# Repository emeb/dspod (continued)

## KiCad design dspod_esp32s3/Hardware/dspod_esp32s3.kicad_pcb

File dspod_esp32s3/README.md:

# dspod_esp32s3

The dspod_esp32s3 is a daughterboard comprising an ESP32 S3 MCU with 4MB Flash, 2MB PSRAM, USB and GPIO + audio I/O.

## Abstract

This board is a small 32-pin device with the following features:

* ESP32S3H4R2 MCU
  - 56-pin QFN package
  - Dual-core Extensa LX7 CPUs 
  - 512kB SRAM
  - USB, I2C, SPI, ADC, GPIO, WiFi, etc on-chip
  - 4MB flash in package
  - 2MB PSRAM in package
* USB-C connector, full-speed host/device
* Nuvoton NAU88C22 stereo codec
* Misc GPIO
  - SPI
  - I2C
  - GPIO
* Four channels of 3.3V multiplexed A/D input
* RF connector for off-board antenna

## Design Materials

* [Schematic](./doc/dspod_esp32s3_sch.pdf)

## Hardware

The hardware design is provided in Kicad 9.x format in the [Hardware](./Hardware) directory.

## Firmware

Firmware is available in the [Firmware](./Firmware) directory.

## Results

The hardware implementation is very similar to an earlier project I did [S3GTA](https://github.com/emeb/S3GTA) so there weren't any big surprises in the overall performance. The CV conversions with the on-chip ADC work fine with a bit of filtering and the encoder/button/LCD-based UI is virtually identical to that on the other three dspod projects so it feels pretty much the same regardless of which instance is in use. The basic effects - filters, delays, reverbs, pitch, frequency and phase shifts - all work the same way and use roughly the right amount of CPU based on their complexity. There are a few unique things about this hardware with respect to the other dspod daughterboards though:

#### PSRAM

The ESP32S3 has a QSPI interface for flash and PSRAM that maps these serial devices into the CPU address space like as though it were internal memory (with slow access times). The H4R2 variant has 2MB PSRAM built in and it works well for audio delay buffering without incurring too much processing overhead.

#### Dual Cores

There are two instances of the Tensilica Extensa LX7 CPU core built in and the vendor's FreeRTOS-based development tools make it very easy to use both. The current effects application code does make use of this, running the UI and ADC code on the first core and the audio DSP on the second core - this hasn't made much difference in overall performance as the current audio code is not particularly taxing, but may help in future experiments that push the boundaries.

#### DSP

The LX7 CPUs have hardware floating point and some vector instructions for accelerating math / DSP operations, and the ESP-IDF has a library of optimized assembly routines for common DSP such as transforms, correlations, windowing, etc. and I've done some experiments with their example code to evaluate the performance. Their radix 4 complex FFT is very efficient, doing better on a per-cycle basis than the ARM CMSIS radix 8 FFT that I use in H7R3 spectral effects. Despite this, the slower processor speed (240MHz max) of the ESP32S3 vs the 600MHz STM32H7R3 means that it cannot complete the required operations within the time allowed so it's not a good match for these algorithms. 

#### RF

Naturally, the ESP32 family has WiFi and Bluetooth capability and I've provided hardware on this board to enable experiments with this. There is a 50-ohm matching network onboard and a uFL connector for use with readily available antennas. Early testing with some of the ESP-IDF WiFi examples indicates that RF performance is sufficient to connect to a nearby AP and the usual APs seen in my area by other devices are visible to the dspod with an inexpensive antenna. 

## Going Further

While I've explored most of the highlights, there are a few aspects of this MCU I'd like to explore further:

#### RF

While WiFi performance appears usable, I'd like to experiment with audio streaming via WiFi and using the dspod as a Bluetooth audio device.

#### Algorithms

The current complement of effects algorithms are fairly lightweight so I'm looking forward to trying out some more complex things, and while spectral processing is probably not practical, there is CPU bandwidth and RAM capacity for more complex time domain effects.

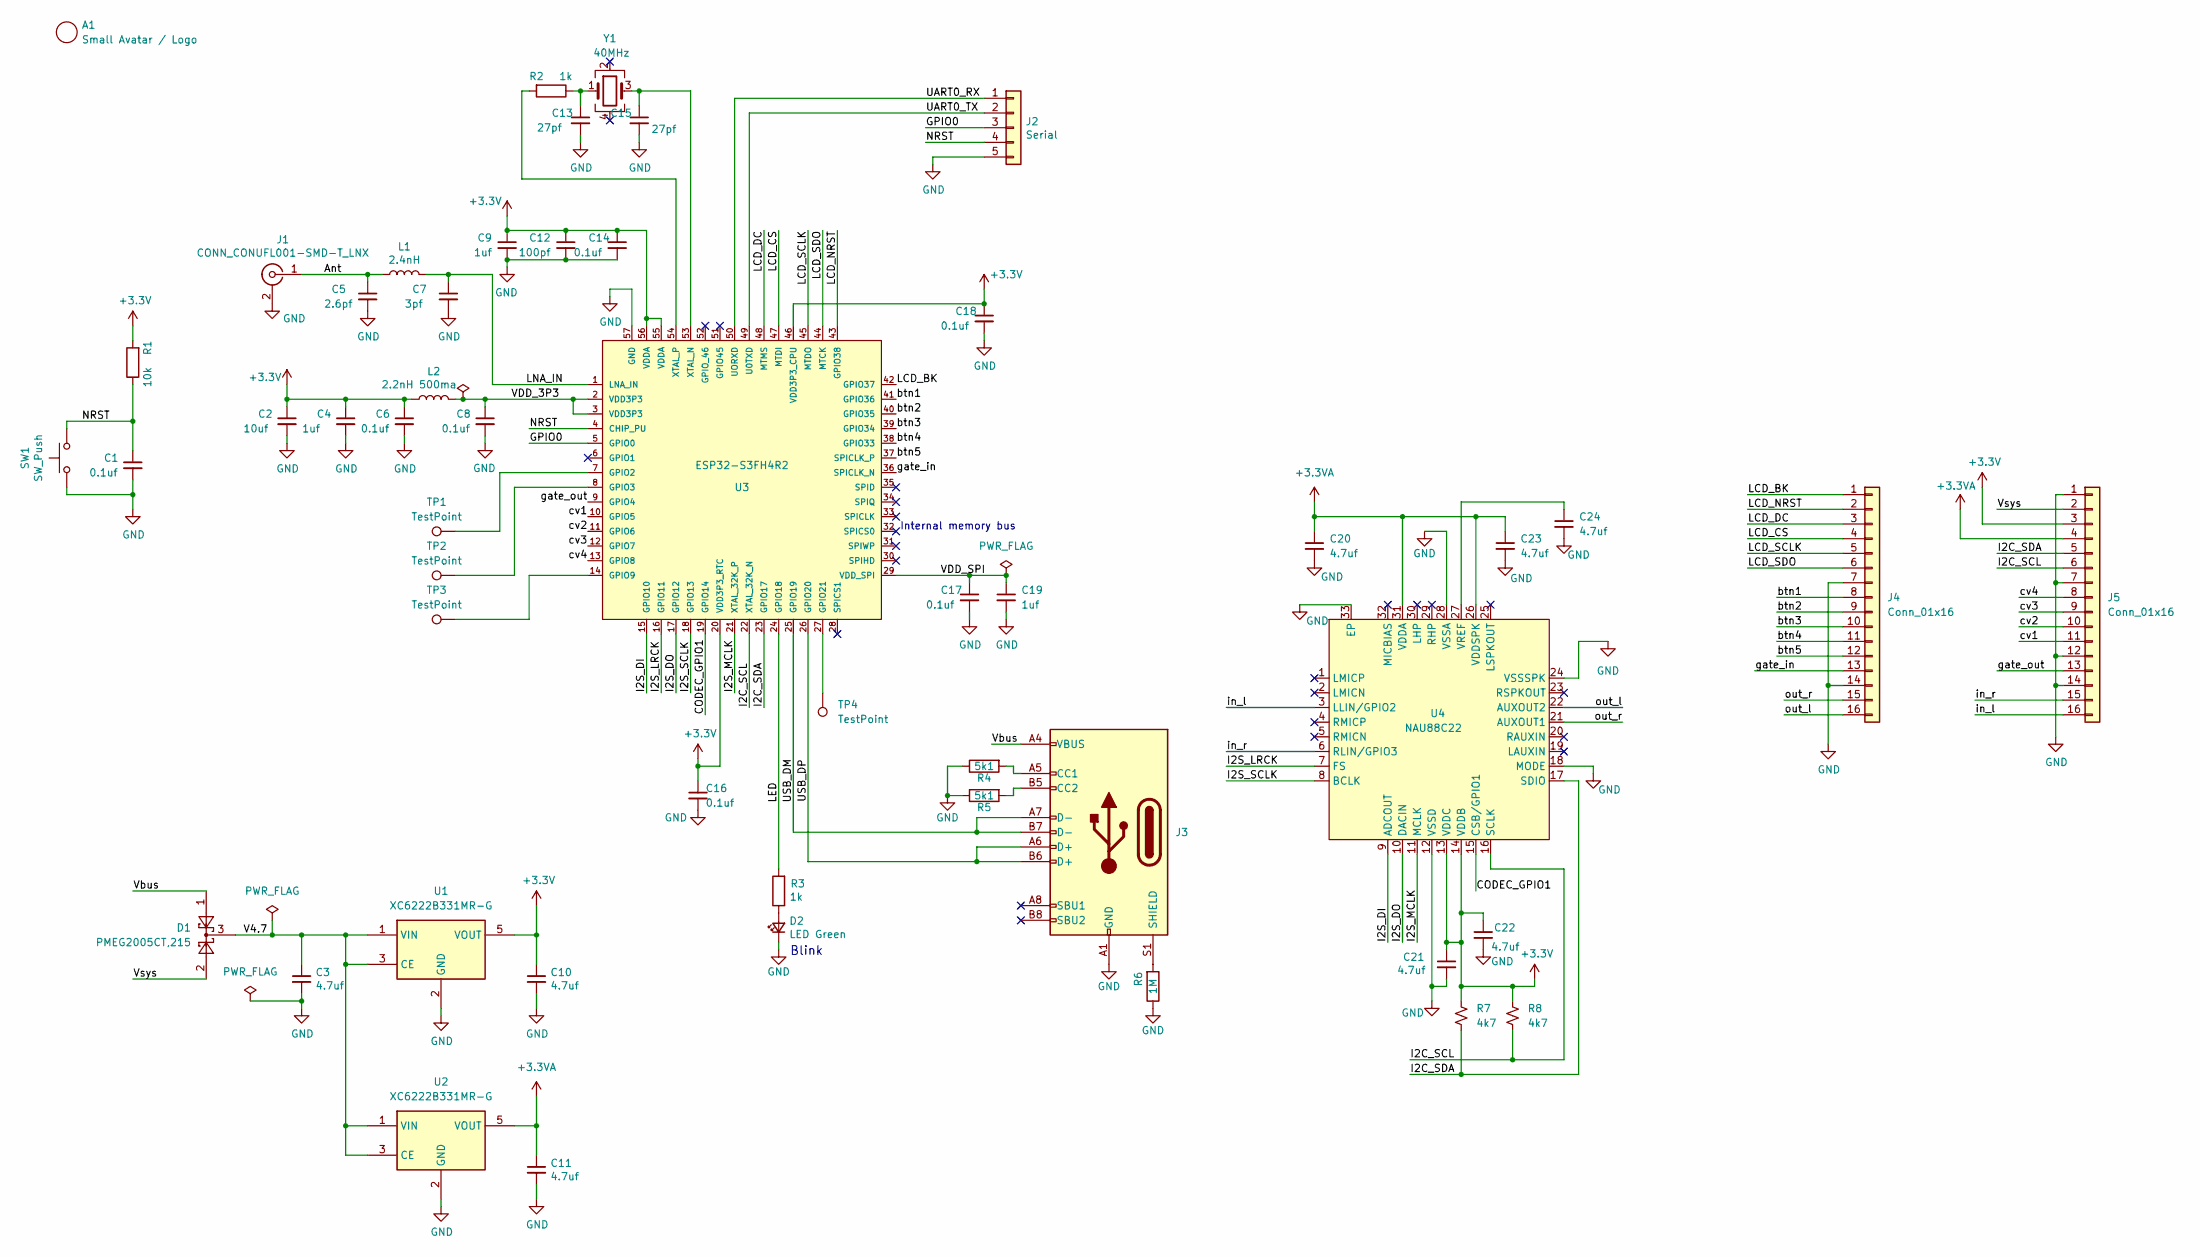
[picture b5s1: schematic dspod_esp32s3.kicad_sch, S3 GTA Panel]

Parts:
A1: Small Avatar / Logo; avatar_small
C1, C6, C8, C14, C16, C17, C18: 0.1uf; C_0402_1005Metric
C2: 10uf; C_0805_2012Metric
C3, C10, C11, C20, C21, C22, C23, C24: 4.7uf; C_0402_1005Metric
C4, C9, C19: 1uf; C_0402_1005Metric
C5: 2.6pf; C_0402_1005Metric
C7: 3pf; C_0402_1005Metric
C12: 100pf; C_0402_1005Metric
C13, C15: 27pf; C_0402_1005Metric
D1: PMEG2005CT,215; SOT-23
D2: LED Green; LED_0603_1608Metric
J1: CONN_CONUFL001-SMD-T_LNX; CONUFL001-SMD-T
J2: Serial; PinHeader_1x05_P2.54mm_Horizontal
J3: USB_C_Receptacle_USB2.0; USB_C_Receptacle_HRO_TYPE-C-31-M-12
J4, J5: Conn_01x16; PinHeader_1x16_P2.54mm_Vertical
L1: 2.4nH; C_0603_1608Metric
L2: 2.2nH 500ma; C_0603_1608Metric
R1: 10k; R_0402_1005Metric
R2, R3: 1k; R_0402_1005Metric
R4, R5: 5k1; R_0402_1005Metric
R6: 1M; R_0402_1005Metric
R7, R8: 4k7; R_0402_1005Metric
SW1: SW_Push; SW_Push_1P1T_NO_CK_KMR2
TP1, TP2, TP3, TP4: TestPoint; TestPoint_Pad_D1.0mm
U1, U2: XC6222B331MR-G; SOT-23-5
U3: ESP32-S3FH4R2; ESP32-S3; mouser part number 356-ESP32-S2; digikey description RX TXRX MOD WIFI SURFACE MOUNT
U4: NAU88C22; QFN-32-1EP_5x5mm_P0.5mm_EP3.1x3.1mm
Y1: 40MHz; Crystal_SMD_3225-4Pin_3.2x2.5mm

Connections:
+3.3V: C2.1, C4.1, C6.1, C9.1, C10.1, C12.1, C14.1, C16.1, C18.1, C21.1, C22.1, J5.3, L2.1, R1.2, R7.2, R8.2, U1.5 (VOUT), U3.20 (VDD3P3_RTC), U3.46 (VDD3P3_CPU), U3.55 (VDDA), U3.56 (VDDA), U4.13 (VDDC), U4.14 (VDDB)
+3.3VA: C11.1, C20.1, C23.1, J5.4, U2.5 (VOUT), U4.26 (VDDSPK), U4.31 (VDDA)
/Ant: C5.1, J1.1 (SIG), L1.1
/CODEC_GPIO1: U3.19 (GPIO14), U4.15 (CSB/GPIO1)
/GPIO0: J2.3, U3.5 (GPIO0)
/I2C_SCL: J5.6, R8.1, U3.22 (XTAL_32K_N), U4.16 (SCLK)
/I2C_SDA: J5.5, R7.1, U3.23 (GPIO17), U4.17 (SDIO)
/I2S_DI: U3.15 (GPIO10), U4.9 (ADCOUT)
/I2S_DO: U3.17 (GPIO12), U4.10 (DACIN)
/I2S_LRCK: U3.16 (GPIO11), U4.7 (FS)
/I2S_MCLK: U3.21 (XTAL_32K_P), U4.11 (MCLK)
/I2S_SCLK: U3.18 (GPIO13), U4.8 (BCLK)
/LCD_BK: J4.1, U3.42 (GPIO37)
/LCD_CS: J4.4, U3.47 (MTDI)
/LCD_DC: J4.3, U3.48 (MTMS)
/LCD_NRST: J4.2, U3.43 (GPIO38)
/LCD_SCLK: J4.5, U3.45 (MTDO)
/LCD_SDO: J4.6, U3.44 (MTCK)
/LED: R3.2, U3.24 (GPIO18)
/LNA_IN: C7.1, L1.2, U3.1 (LNA_IN)
/NRST: C1.1, J2.4, R1.1, SW1.1, U3.4 (CHIP_PU)
/UART0_RX: J2.1, U3.50 (UORXD)
/UART0_TX: J2.2, U3.49 (U0TXD)
/USB_DM: J3.A7 (D-), J3.B7 (D-), U3.25 (GPIO19)
/USB_DP: J3.A6 (D+), J3.B6 (D+), U3.26 (GPIO20)
/V4.7: C3.1, D1.3, U1.1 (VIN), U1.3 (CE), U2.1 (VIN), U2.3 (CE)
/VDD_3P3: C8.1, L2.2, U3.2 (VDD3P3), U3.3 (VDD3P3)
/VDD_SPI: C17.1, C19.1, U3.29 (VDD_SPI)
/Vbus: D1.1, J3.A4 (VBUS), J3.A9 (VBUS), J3.B4 (VBUS), J3.B9 (VBUS)
/Vsys: D1.2, J5.2
/btn1: J4.8, U3.41 (GPIO36)
/btn2: J4.9, U3.40 (GPIO35)
/btn3: J4.10, U3.39 (GPIO34)
/btn4: J4.11, U3.38 (GPIO33)
/btn5: J4.12, U3.37 (SPICLK_P)
/cv1: J5.11, U3.10 (GPIO5)
/cv2: J5.10, U3.11 (GPIO6)
/cv3: J5.9, U3.12 (GPIO7)
/cv4: J5.8, U3.13 (GPIO8)
/gate_in: J4.13, U3.36 (SPICLK_N)
/gate_out: J5.13, U3.9 (GPIO4)
/in_l: J5.16, U4.3 (LLIN/GPIO2)
/in_r: J5.15, U4.6 (RLIN/GPIO3)
/out_l: J4.16, U4.22 (AUXOUT2)
/out_r: J4.15, U4.21 (AUXOUT1)
GND: C1.2, C2.2, C3.2, C4.2, C5.2, C6.2, C7.2, C8.2, C9.2, C10.2, C11.2, C12.2, C13.2, C14.2, C15.2, C16.2, C17.2, C18.2, C19.2, C20.2, C21.2, C22.2, C23.2, C24.2, D2.1 (K), J1.2 (GND), J2.5, J3.A1 (GND), J3.A12 (GND), J3.B1 (GND), J3.B12 (GND), J4.7, J4.14, J5.1, J5.7, J5.12, J5.14, R4.1, R5.1, R6.1, SW1.2, U1.2 (GND), U2.2 (GND), U3.57 (GND), U4.12 (VSSD), U4.18 (MODE), U4.24 (VSSSPK), U4.28 (VSSA), U4.33 (EP)
unnamed: C13.1, R2.1, Y1.1
unnamed: D2.2 (A), R3.1
unnamed: J3.A5 (CC1), R4.2
unnamed: J3.B5 (CC2), R5.2
unnamed: J3.S1 (SHIELD), R6.2
unnamed: TP1.1, U3.7 (GPIO2)
unnamed: TP2.1, U3.8 (GPIO3)
unnamed: TP3.1, U3.14 (GPIO9)
unnamed: TP4.1, U3.27 (GPIO21)
unnamed: C15.1, U3.53 (XTAL_N), Y1.3
unnamed: R2.2, U3.54 (XTAL_P)
unnamed: C24.1, U4.27 (VREF)

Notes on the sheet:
Internal memory bus
Blink

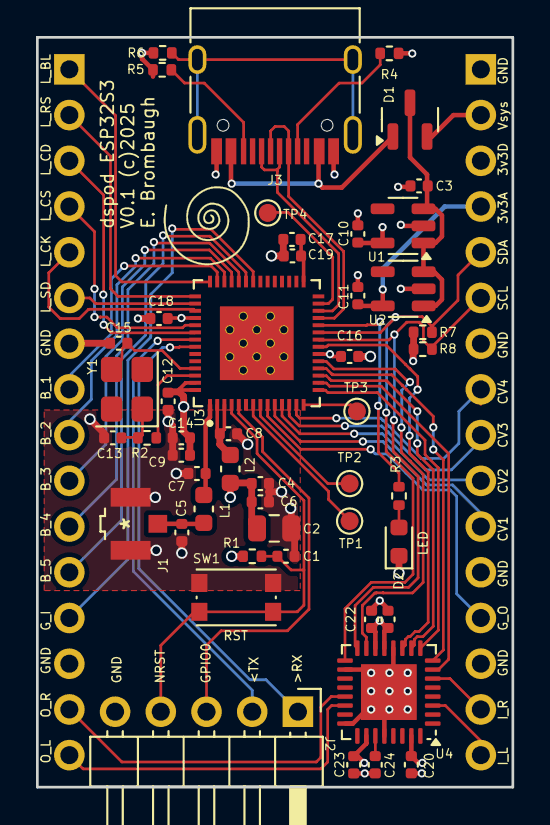
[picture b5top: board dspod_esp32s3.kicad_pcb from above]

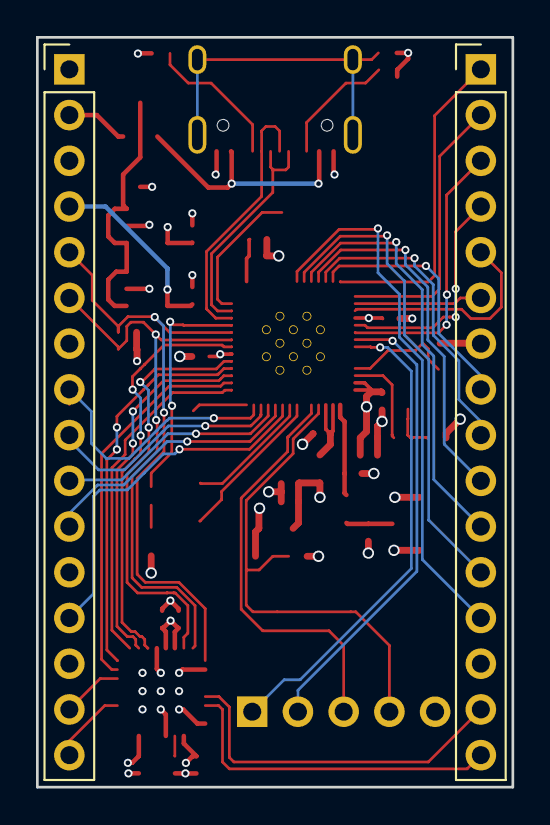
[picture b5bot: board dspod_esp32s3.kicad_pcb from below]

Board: 4 copper layers, 26.4 x 41.7 mm, 52 parts (2 on the bottom side), 58 nets.

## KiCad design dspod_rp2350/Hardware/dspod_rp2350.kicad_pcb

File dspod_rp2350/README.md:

# dspod_rp2350

The dspod_rp2350 is a daughterboard comprising an RP2350A MCU with 4MB Flash, 8MB PSRAM, USB and GPIO + audio I/O.

## Abstract

This board is a small 32-pin device with the following features:

* RP2350 MCU
  - 68-pin QFN package
  - Dual-core Arm Cortex M33 or Hazard3 RISC-V CPUs 
  - 520kB SRAM
  - USB, I2C, SPI, ADC, GPIO, PIO, etc on-chip
* USB-C connector, full-speed host/device
* Nuvoton NAU88C22 stereo codec
* Misc GPIO
  - SPI
  - I2C
  - GPIO
* Four channels of 3.3V multiplexed A/D input

## Design Materials

* [Schematic](./doc/dspod_rp2350_sch.pdf)
* [BOM Spreadsheet](./doc/dspod_rp2350_BOM.ods)

## Hardware

The hardware design is provided in Kicad 9.x format in the [Hardware](./Hardware) directory.

## Firmware

A collection of test programs for exercising all the peripherals of the dspod_rp2350 can be found in the [Firmware](./Firmware) directory.

## Results

Bringing up the hardware drivers and DSP effects application on the RP2350 was remarkably pain-free and performance is reasonable given the manufacturer's published constraints. Following are some observations:

#### I2S Audio

The PIO peripheral works well for implementing I2S formatted serial I/O with DMA into on-chip SRAM buffers. I use a slightly modified version of the original output-only example code that was provided by the manufacturer and was adapted for full-duplex operation by [Jonathan Brodsky](https://github.com/jonbro). 

#### Multicore processing

This is well-supported by the Pico SDK and straightforward to implement. In the DSP effects application the code was split between the foreground UI and ADC polling running on core 0 and the DSP running on core 1 which worked nicely.

#### PSRAM

The original RP2040 relies on external QSPI flash for nonvolatile storage of code and data and allows execute in-place (XIP) access which maps the external QSPI flash into the CPU address space. This works very well and for the RP2350 a second chip select line and write capability was added that supports RAM. This board uses that capability for audio data buffering and it functions well.

#### Loadable code

An experiment in the effects application was the use of loadable code sections via "overlays". This requires some fancy tricks in the linker and function attributes to pull chunks of executable code from off-chip flash into on-chip CCMRAM on demand in order to improve code execution speed while limiting the resources required for large code bases. This worked well and allows maximum code execution speed while not impacting RAM usage heavily.

#### Clock Speed

As of February 2026, the RP2350 is specified to run at a maximum clock speed of 150MHz with a VREG voltage of 1.1V. Experiments in the user community have shown however that it can be reliably run at much higher speeds if the VREG setting is increased and proper cooling is provided - see this article for details: [Overclocking Raspberry Pi Pico 2](https://learn.pimoroni.com/article/overclocking-the-pico-2). By default, the dspod_rp2350 is set to operate at 159.750MHz - slightly overclocked to provide a nearly perfect 48001Hz audio sample rate, but by changing a few settings in the CMakelists.txt file it's possible to double the clock rate to nearly 320MHz with only a slight increase in the VREG setting (firmware controlled) which significantly improves the CPU loading of the more complex DSP. Further increases may be possible, and if rates near 500MHz are acheivable then FFT-based spectral effects may be feasible on this platform. Further experiments are in process to see where the limits are. 

#### Performance

Overall, the RP2350 platform provides a lot of powerful options for audio DSP, especially if pushed beyond the conservative limits specified by the manufacturer. The MCU itself is one of the least expensive ones tested on the dspod ecosystem despite providing two CPU cores and lots of on-chip SRAM and it has a lot of potential that hasn't been fully explored.

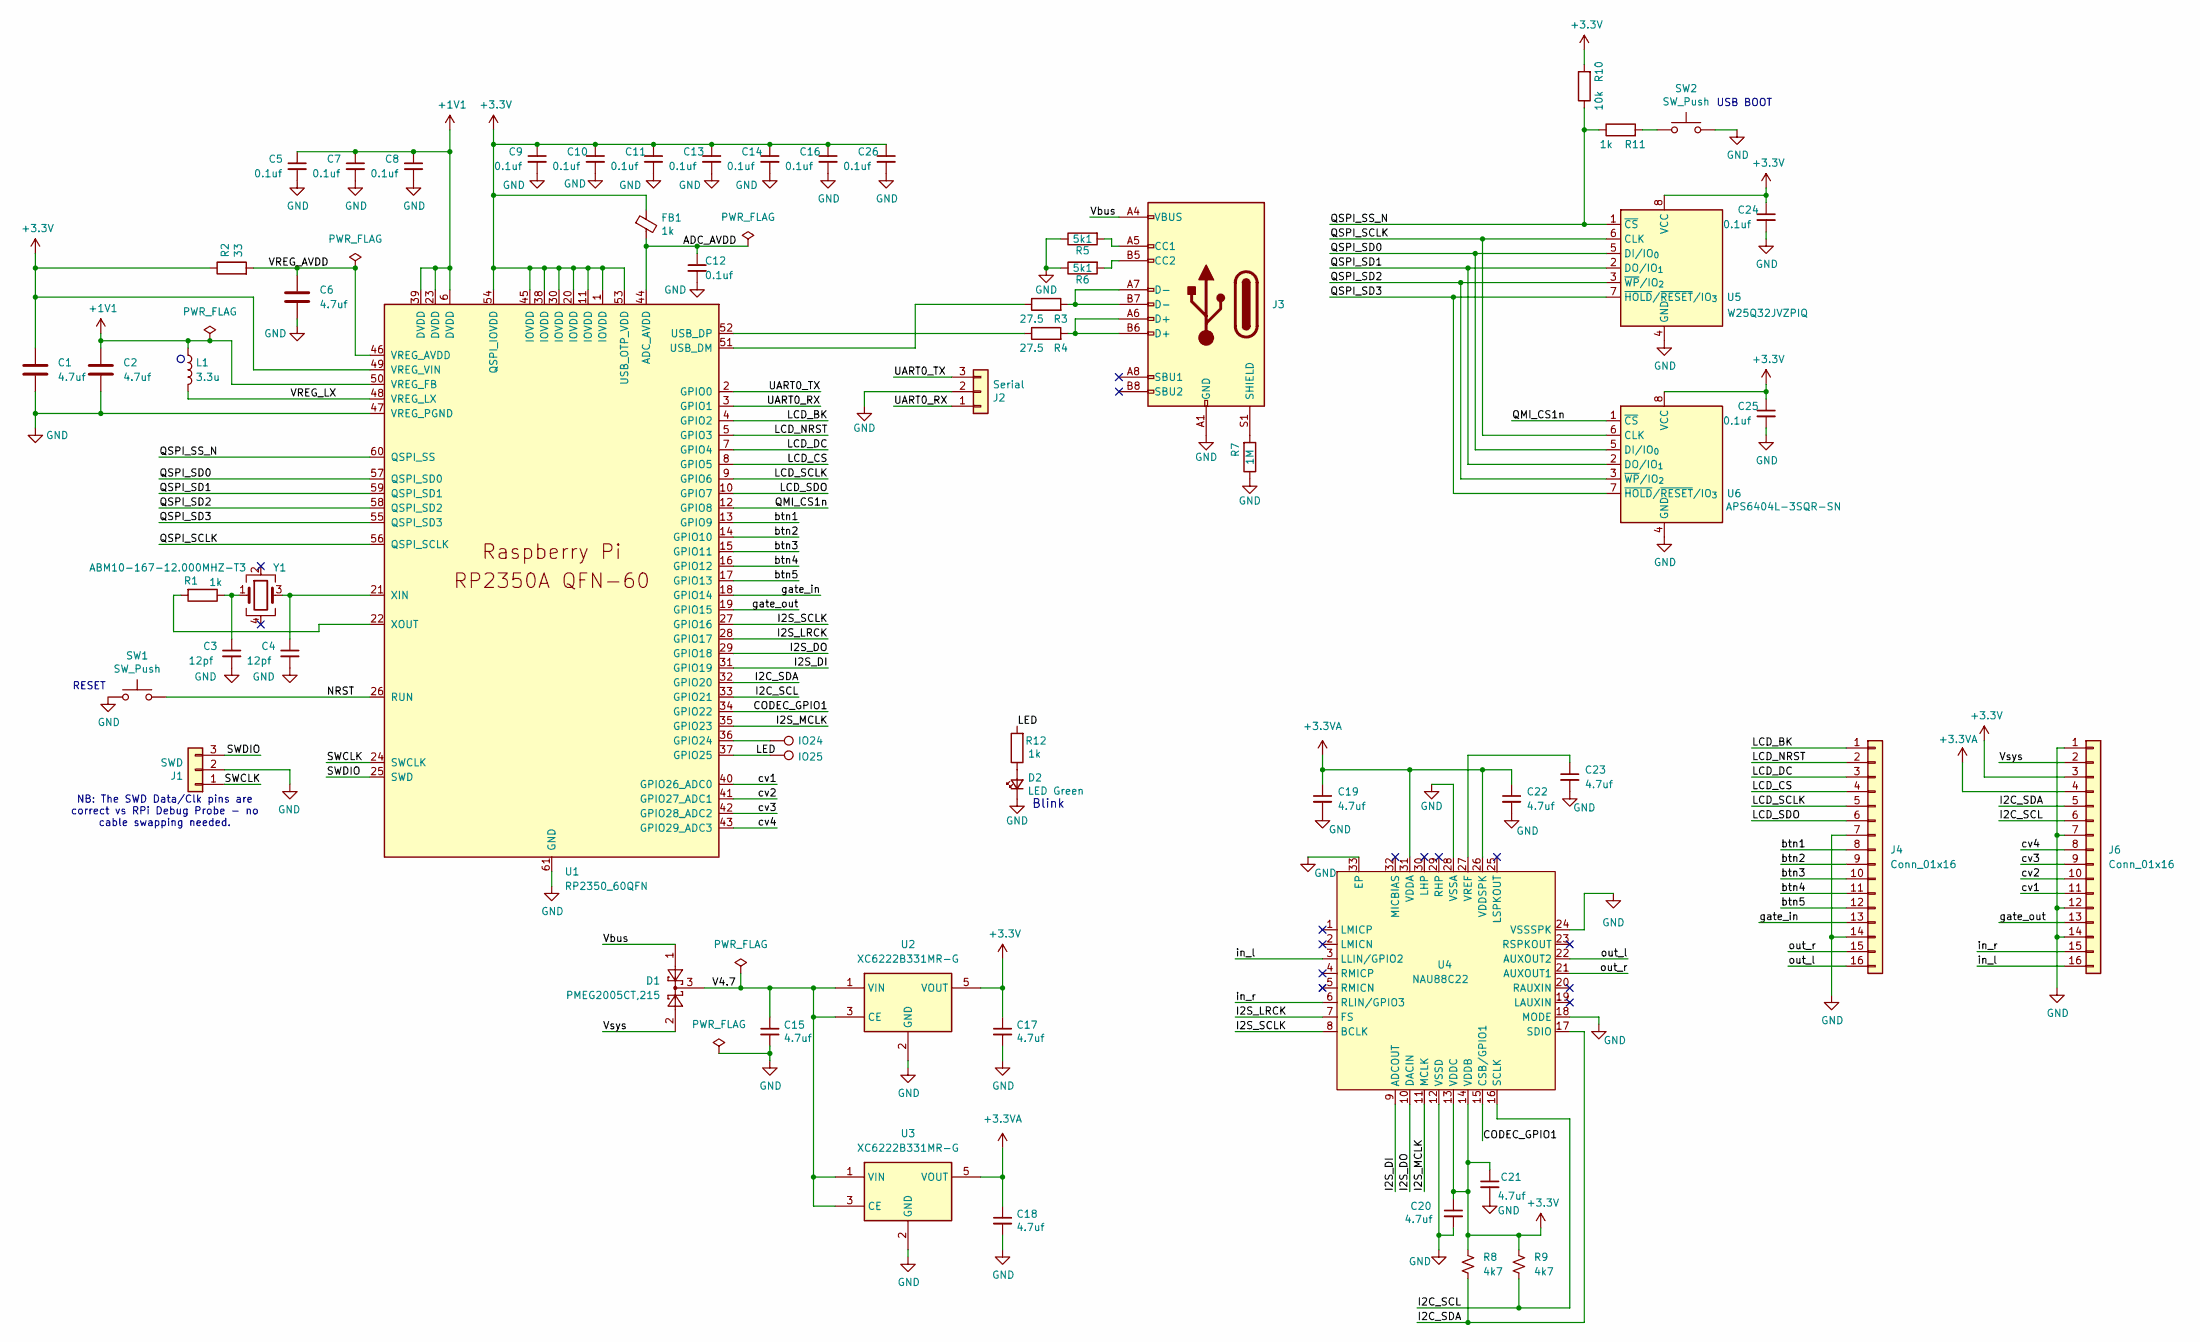
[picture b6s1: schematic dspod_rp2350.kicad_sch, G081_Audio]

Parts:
C1, C2: 4.7uf; C_0402_1005Metric_small_pads
C3, C4: 12pf; C_0402_1005Metric
C5, C7, C8, C9, C10, C11, C12, C13, C14, C16, C24, C25, C26: 0.1uf; C_0402_1005Metric
C6, C15, C17, C18, C19, C20, C21, C22, C23: 4.7uf; C_0402_1005Metric
D1: PMEG2005CT,215; SOT-23
D2: LED Green; LED_0603_1608Metric
FB1: 1k; L_0603_1608Metric
J1: SWD; JST_SH_SM03B-SRSS-TB_1x03-1MP_P1.00mm_Horizontal
J2: Serial; JST_SH_SM03B-SRSS-TB_1x03-1MP_P1.00mm_Horizontal
J3: USB_C_Receptacle_USB2.0; USB_C_Receptacle_HRO_TYPE-C-31-M-12
J4, J6: Conn_01x16; PinHeader_1x16_P2.54mm_Vertical
L1: 3.3u; L_pol_2016
R1, R11, R12: 1k; R_0402_1005Metric
R2: 33; R_0402_1005Metric
R3, R4: 27.5; R_0402_1005Metric
R5, R6: 5k1; R_0402_1005Metric
R7: 1M; R_0402_1005Metric
R8, R9: 4k7; R_0402_1005Metric
R10: 10k; R_0402_1005Metric
SW1, SW2: SW_Push; SW_SPST_PTS815
TP1: IO24; TestPoint_Pad_D1.0mm
TP2: IO25; TestPoint_Pad_D1.0mm
U1: RP2350_60QFN; RP2350-QFN-60-1EP_7x7_P0.4mm_EP3.4x3.4mm_ThermalVias
U2, U3: XC6222B331MR-G; SOT-23-5
U4: NAU88C22; QFN-32-1EP_5x5mm_P0.5mm_EP3.1x3.1mm
U5: W25Q32JVZPIQ; WSON-8-1EP_6x5mm_P1.27mm_EP3.4x4.3mm
U6: APS6404L-3SQR-SN; SOIC-8_3.9x4.9mm_P1.27mm
Y1: ABM10-167-12.000MHZ-T3; Crystal_SMD_2520-4Pin_2.5x2.0mm

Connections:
+1V1: C2.1, C5.1, C7.1, C8.1, L1.1, U1.6 (DVDD), U1.23 (DVDD), U1.39 (DVDD), U1.50 (VREG_FB)
+3.3V: C1.1, C9.1, C10.1, C11.1, C13.1, C14.1, C16.1, C17.1, C20.1, C21.1, C24.1, C25.1, C26.1, FB1.1, J6.3, R2.1, R8.2, R9.2, R10.2, U1.1 (IOVDD), U1.11 (IOVDD), U1.20 (IOVDD), U1.30 (IOVDD), U1.38 (IOVDD), U1.45 (IOVDD), U1.49 (VREG_VIN), U1.53 (USB_OTP_VDD), U1.54 (QSPI_IOVDD), U2.5 (VOUT), U4.13 (VDDC), U4.14 (VDDB), U5.8 (VCC), U6.8 (VCC)
+3.3VA: C18.1, C19.1, C22.1, J6.4, U3.5 (VOUT), U4.26 (VDDSPK), U4.31 (VDDA)
/ADC_AVDD: C12.1, FB1.2, U1.44 (ADC_AVDD)
/CODEC_GPIO1: U1.34 (GPIO22), U4.15 (CSB/GPIO1)
/I2C_SCL: J6.6, R9.1, U1.33 (GPIO21), U4.16 (SCLK)
/I2C_SDA: J6.5, R8.1, U1.32 (GPIO20), U4.17 (SDIO)
/I2S_DI: U1.31 (GPIO19), U4.9 (ADCOUT)
/I2S_DO: U1.29 (GPIO18), U4.10 (DACIN)
/I2S_LRCK: U1.28 (GPIO17), U4.7 (FS)
/I2S_MCLK: U1.35 (GPIO23), U4.11 (MCLK)
/I2S_SCLK: U1.27 (GPIO16), U4.8 (BCLK)
/LCD_BK: J4.1, U1.4 (GPIO2)
/LCD_CS: J4.4, U1.8 (GPIO5)
/LCD_DC: J4.3, U1.7 (GPIO4)
/LCD_NRST: J4.2, U1.5 (GPIO3)
/LCD_SCLK: J4.5, U1.9 (GPIO6)
/LCD_SDO: J4.6, U1.10 (GPIO7)
/LED: R12.2, TP2.1, U1.37 (GPIO25)
/NRST: SW1.2, U1.26 (RUN)
/QMI_CS1n: U1.12 (GPIO8), U6.1 (~CS)
/QSPI_SCLK: U1.56 (QSPI_SCLK), U5.6 (CLK), U6.6 (CLK)
/QSPI_SD0: U1.57 (QSPI_SD0), U5.5 (DI(IO0)), U6.5 (DI(IO0))
/QSPI_SD1: U1.59 (QSPI_SD1), U5.2 (DO(IO1)), U6.2 (DO(IO1))
/QSPI_SD2: U1.58 (QSPI_SD2), U5.3 (IO2), U6.3 (IO2)
/QSPI_SD3: U1.55 (QSPI_SD3), U5.7 (IO3), U6.7 (IO3)
/QSPI_SS_N: R10.1, R11.1, U1.60 (QSPI_SS), U5.1 (~CS)
/SWCLK: J1.1, U1.24 (SWCLK)
/SWDIO: J1.3, U1.25 (SWD)
/UART0_RX: J2.1, U1.3 (GPIO1)
/UART0_TX: J2.3, U1.2 (GPIO0)
/V4.7: C15.1, D1.3, U2.1 (VIN), U2.3 (CE), U3.1 (VIN), U3.3 (CE)
/VREG_AVDD: C6.1, R2.2, U1.46 (VREG_AVDD)
/VREG_LX: L1.2, U1.48 (VREG_LX)
/Vbus: D1.1, J3.A4 (VBUS), J3.A9 (VBUS), J3.B4 (VBUS), J3.B9 (VBUS)
/Vsys: D1.2, J6.2
/btn1: J4.8, U1.13 (GPIO9)
/btn2: J4.9, U1.14 (GPIO10)
/btn3: J4.10, U1.15 (GPIO11)
/btn4: J4.11, U1.16 (GPIO12)
/btn5: J4.12, U1.17 (GPIO13)
/cv1: J6.11, U1.40 (GPIO26_ADC0)
/cv2: J6.10, U1.41 (GPIO27_ADC1)
/cv3: J6.9, U1.42 (GPIO28_ADC2)
/cv4: J6.8, U1.43 (GPIO29_ADC3)
/gate_in: J4.13, U1.18 (GPIO14)
/gate_out: J6.13, U1.19 (GPIO15)
/in_l: J6.16, U4.3 (LLIN/GPIO2)
/in_r: J6.15, U4.6 (RLIN/GPIO3)
/out_l: J4.16, U4.22 (AUXOUT2)
/out_r: J4.15, U4.21 (AUXOUT1)
GND: C1.2, C2.2, C3.2, C4.2, C5.2, C6.2, C7.2, C8.2, C9.2, C10.2, C11.2, C12.2, C13.2, C14.2, C15.2, C16.2, C17.2, C18.2, C19.2, C20.2, C21.2, C22.2, C23.2, C24.2, C25.2, C26.2, D2.1 (K), J1.2, J2.2, J3.A1 (GND), J3.A12 (GND), J3.B1 (GND), J3.B12 (GND), J4.7, J4.14, J6.1, J6.7, J6.12, J6.14, R5.1, R6.1, R7.1, SW1.1, SW2.2, U1.47 (VREG_PGND), U1.61 (GND), U2.2 (GND), U3.2 (GND), U4.12 (VSSD), U4.18 (MODE), U4.24 (VSSSPK), U4.28 (VSSA), U4.33 (EP), U5.4 (GND), U6.4 (GND)
unnamed: C3.1, R1.1, Y1.1
unnamed: D2.2 (A), R12.1
unnamed: J3.A5 (CC1), R5.2
unnamed: J3.B5 (CC2), R6.2
unnamed: J3.A6 (D+), J3.B6 (D+), R4.2
unnamed: J3.A7 (D-), J3.B7 (D-), R3.2
unnamed: J3.S1 (SHIELD), R7.2
unnamed: R11.2, SW2.1
unnamed: TP1.1, U1.36 (GPIO24)
unnamed: R3.1, U1.51 (USB_DM)
unnamed: R4.1, U1.52 (USB_DP)
unnamed: C4.1, U1.21 (XIN), Y1.3
unnamed: R1.2, U1.22 (XOUT)
unnamed: C23.1, U4.27 (VREF)

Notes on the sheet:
USB BOOT
Blink
RESET
NB: The SWD Data/Clk pins are correct vs RPi Debug Probe - no cable swapping needed.

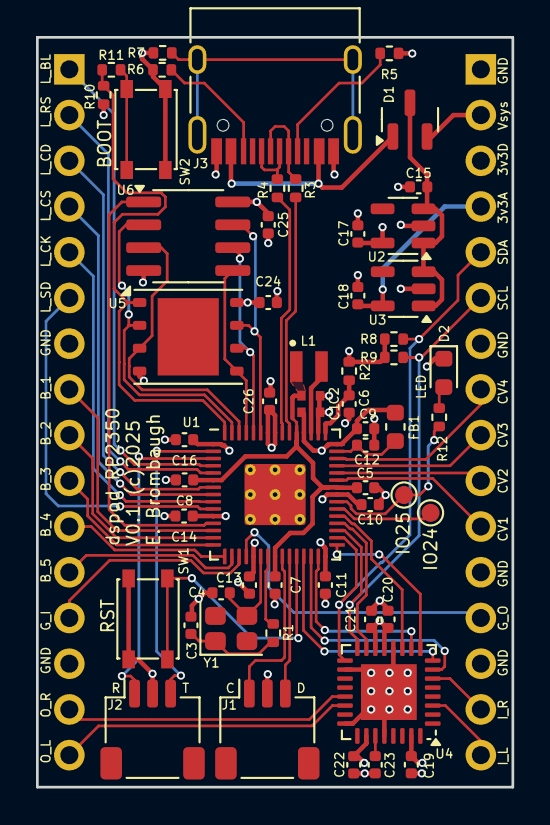
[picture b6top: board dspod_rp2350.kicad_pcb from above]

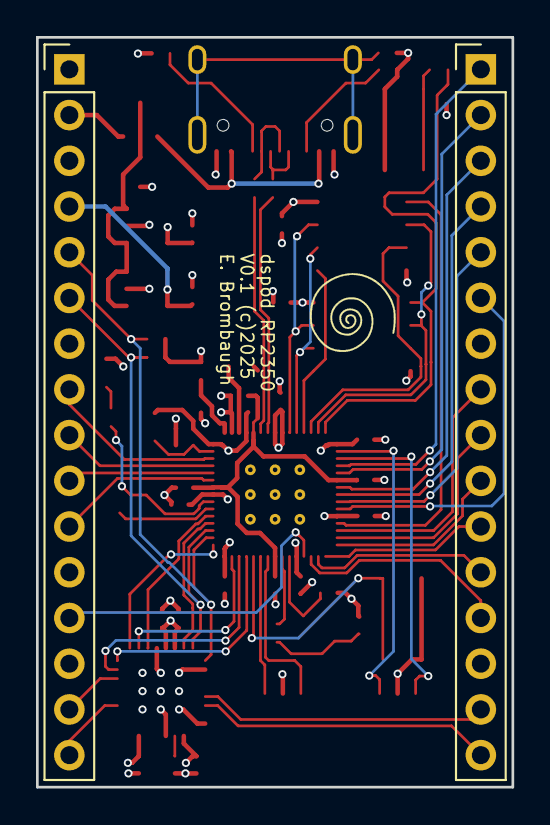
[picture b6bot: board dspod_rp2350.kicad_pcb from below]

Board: 4 copper layers, 26.4 x 41.7 mm, 59 parts (3 on the bottom side), 66 nets.

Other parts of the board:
Ref**: Val**; avatar_small
